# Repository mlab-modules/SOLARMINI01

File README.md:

[Czech](./README.cs.md)
<!--- module --->
# SOLARMINI01A
<!--- Emodule --->

<!--- subtitle ---> MPPT module for up to 5 Watt photovoltaic panel.<!--- Esubtitle --->

<!--- description ---> Module permanently search maximum power point of connected photovoltaic panel and convert the generated energy to higher voltages (5V maximum). It can be used for single cell or few serial connected cells. <!--- Edescription --->

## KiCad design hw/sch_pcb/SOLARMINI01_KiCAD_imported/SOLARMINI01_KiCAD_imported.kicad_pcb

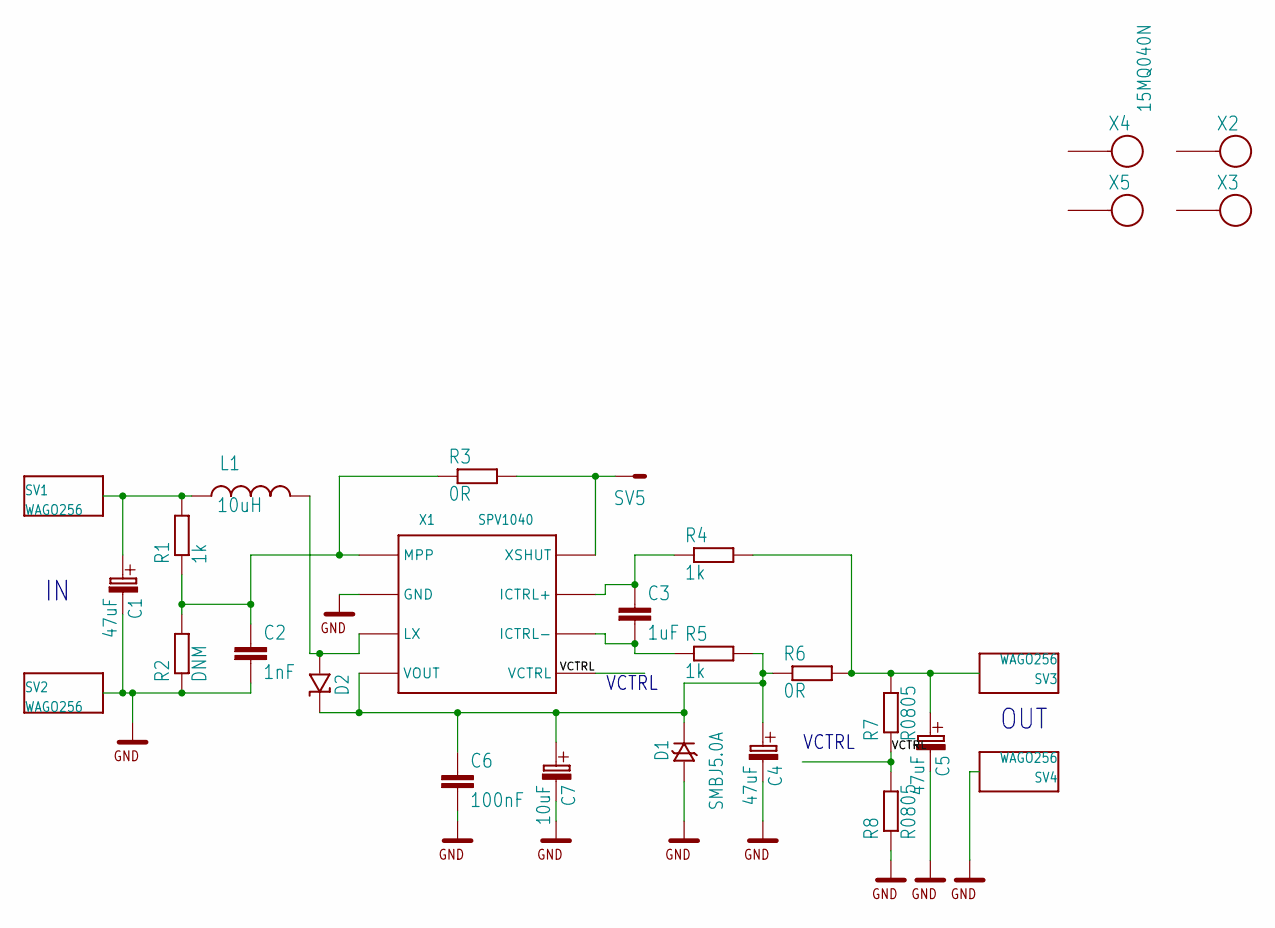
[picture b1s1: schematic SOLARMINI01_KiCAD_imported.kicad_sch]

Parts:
C1, C4, C5: 47uF; C
C2: 1nF; C0805
C3: 1uF; C0805
C6: 100nF; C0805
C7: 10uF; B
D1: SMBJ5.0A; SMB
D2: 15MQ040N; SMA
L1: 10uH; DE1205-10
R1, R4, R5: 1k; 0805
R2: DNM; 0805
R3, R6: 0R; 1206
R7, R8: R0805; 0805
SV1, SV2, SV3, SV4: WAGO256
SV5: MA01-1
X1: SPV1040; TSSOP8
X2, X3, X4, X5: SROUB3M

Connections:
GND: C1.- (C_EL-), C2.2, C4.- (C_EL-), C5.- (C_EL-), C6.2, C7.- (C_EL-), D1.A, R2.1, R8.1, SV2.1, SV2.A1, SV4.1, SV4.A1, X1.2 (GND)
unnamed: C1.+ (C_EL+), L1.P$1 (1), R1.2, SV1.1, SV1.A1
unnamed: R3.2, SV5.1, X1.8 (XSHUT)
unnamed: C2.1, R1.1, R2.2, R3.1, X1.1 (MPP)
unnamed: C3.1, R4.1, X1.7 (ICTRL+)
unnamed: C4.+ (C_EL+), C6.1, C7.+ (C_EL+), D1.K, D2.K, R5.2, R6.1, X1.4 (VOUT)
unnamed: D2.A, L1.P$2 (2), X1.3 (LX)
unnamed: C5.+ (C_EL+), R4.2, R6.2, R7.2, SV3.1, SV3.A1
unnamed: C3.2, R5.1, X1.6 (ICTRL-)
VCTRL: R7.1, R8.2, X1.5 (VCTRL)

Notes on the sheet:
VCTRL
OUT

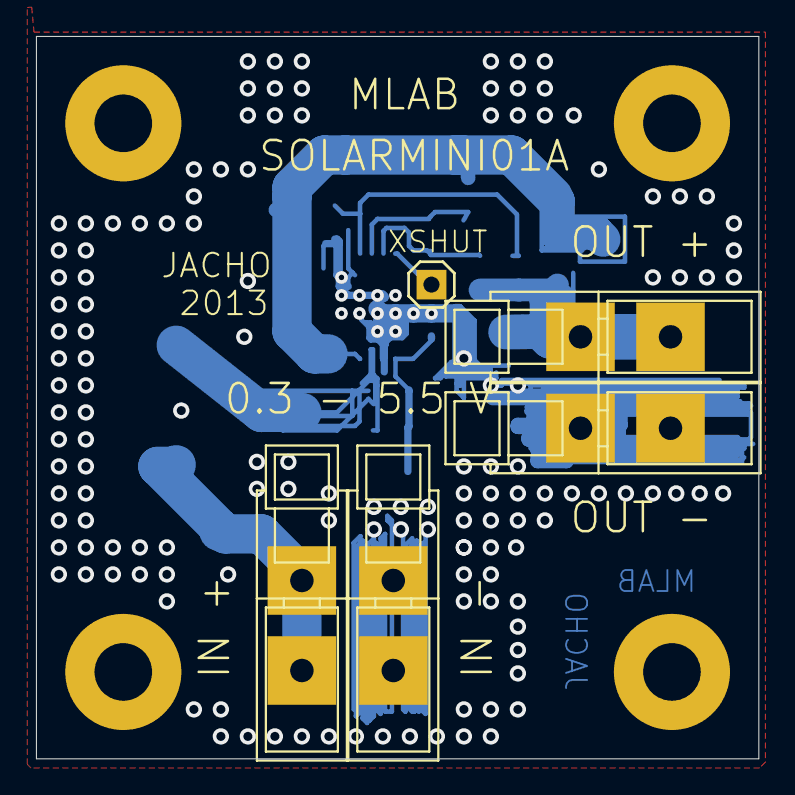
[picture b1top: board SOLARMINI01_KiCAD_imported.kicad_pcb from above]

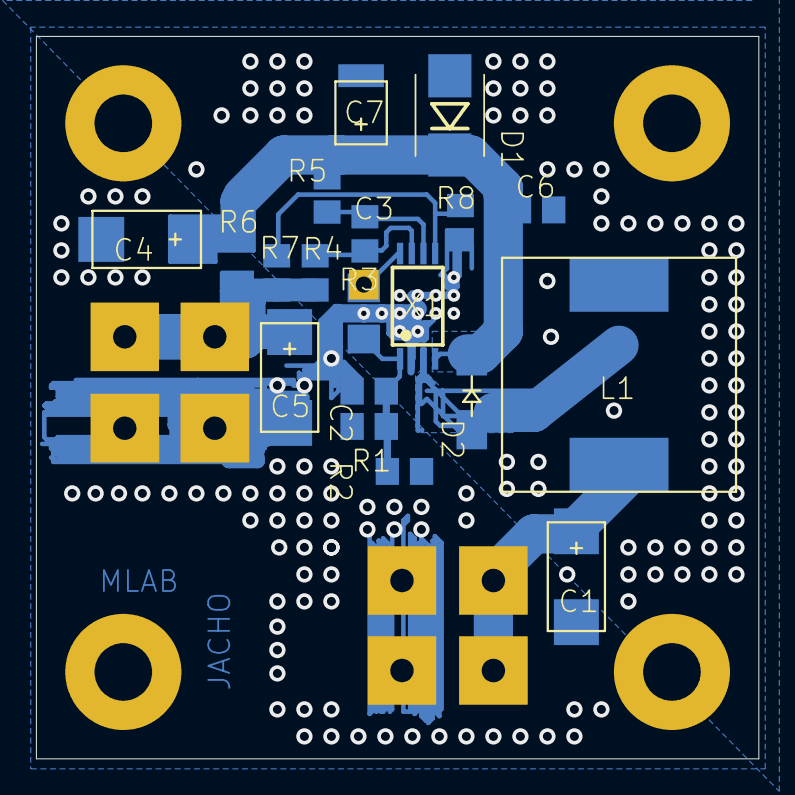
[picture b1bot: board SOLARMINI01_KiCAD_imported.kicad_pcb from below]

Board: 2 copper layers, 40.1 x 40.1 mm, 28 parts (19 on the bottom side), 10 nets.

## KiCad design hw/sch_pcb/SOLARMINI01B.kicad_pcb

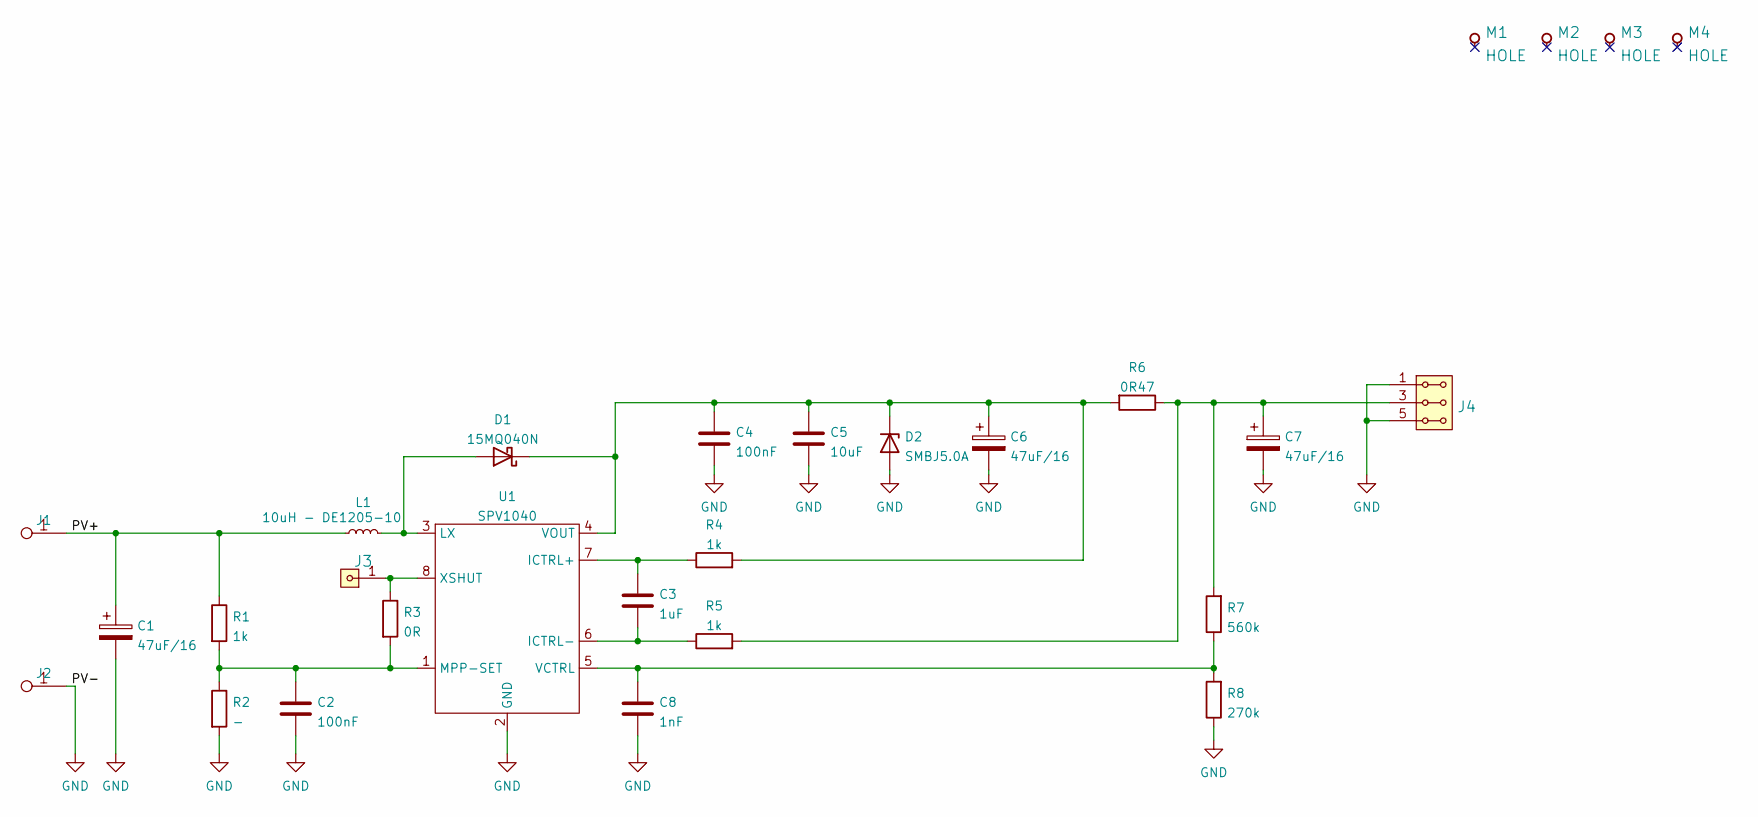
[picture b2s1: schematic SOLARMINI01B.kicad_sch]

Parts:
C1, C6, C7: 47uF/16; TantalC_SizeC_Reflow
C2, C4: 100nF; C_0805_2012Metric
C3: 1uF; C_0805_2012Metric
C5: 10uF; C_0805_2012Metric
C8: 1nF; C_0805_2012Metric
D1: 15MQ040N; D_SMA
D2: SMBJ5.0A; D_SMA
J1: WAGO 256 RED; WAGO256
J2: WAGO 256 BLUE; WAGO256
J3: HEADER_1x01; Straight_1x01
J4: HEADER_2x03_PARALLEL; Straight_2x03
L1: 10uH - DE1205-10; DE1205-10
M1, M2, M3, M4: HOLE; MountingHole_3mm
R1, R4, R5: 1k; R_0805_2012Metric
R2: -; R_0805_2012Metric
R3: 0R; R_0805_2012Metric
R6: 0R47; R_1206_3216Metric
R7: 560k; R_0805_2012Metric
R8: 270k; R_0805_2012Metric
U1: SPV1040; TSSOP-8_4.4x3mm_P0.65mm

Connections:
/PV+: C1.1, J1.1, L1.1, R1.1
GND: C1.2, C2.2, C4.2, C5.2, C6.2, C7.2, C8.2, D2.2 (A), J2.1, J4.1, J4.2, J4.5, J4.6, R2.2, R8.1, U1.2 (GND)
unnamed: C2.1, R1.2, R2.1, R3.2, U1.1 (MPP-SET)
unnamed: C3.1, R4.1, U1.7 (ICTRL+)
unnamed: C3.2, R5.1, U1.6 (ICTRL-)
unnamed: C4.1, C5.1, C6.1, D1.1 (K), D2.1 (K), R4.2, R6.2, U1.4 (VOUT)
unnamed: C7.1, J4.3, J4.4, R5.2, R6.1, R7.2
unnamed: C8.1, R7.1, R8.2, U1.5 (VCTRL)
unnamed: D1.2 (A), L1.2, U1.3 (LX)
unnamed: J3.1, R3.1, U1.8 (XSHUT)

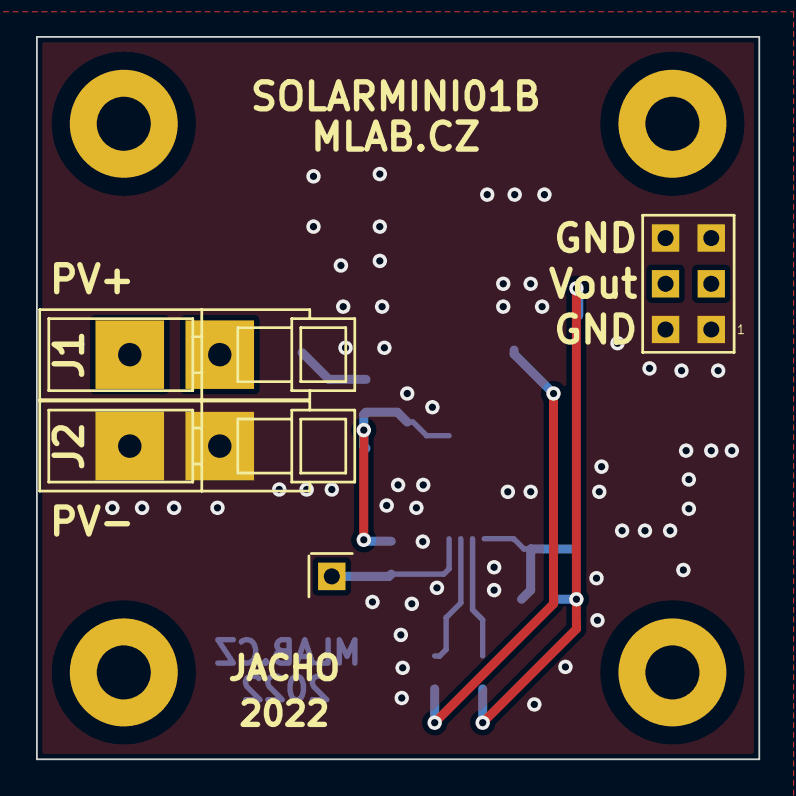
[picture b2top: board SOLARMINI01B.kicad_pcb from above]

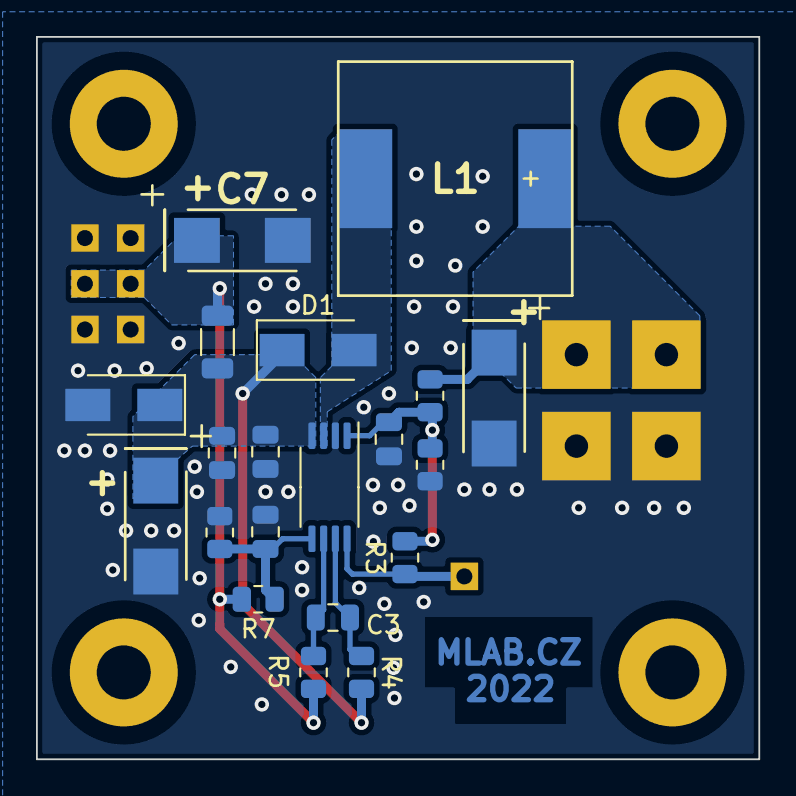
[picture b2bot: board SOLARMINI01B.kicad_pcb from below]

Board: 2 copper layers, 40.1 x 40.1 mm, 28 parts (20 on the bottom side), 10 nets.

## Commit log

2017-08-22 rename category folders
2017-08-22 rename files and module folders
2017-08-22 change images path
2017-08-22 create hw folder
2017-08-22 change filepaths
2017-08-22 new .json files
2017-11-16 [MLABweb] 2017-11-16 11:42:35 SOLARMINI01A
2018-11-05 Presun obrazku do slozky img. Pregenerovani dokumentaci.
2021-12-20 Edit schema in KiCAD
2021-12-20 Edit strukture
2021-12-20 edit schema
2021-12-20 Edit PCB
2021-12-22 Úpravy PCB a generování výrobních dat.
2021-12-22 Edit BOM
2022-01-03 Osazovací předpis
2022-02-07 Update module documentation.
2022-04-06 automated commit; add github actions
2022-04-06 Update actions products
2023-05-14 Convert project to KiCAD.
2023-05-25 Update metadata files
2023-05-28 Update workflow files
2023-07-05 automated commit; rename source files to new naming convence
2023-09-16 Update image to image_title
2023-09-16 Update status
